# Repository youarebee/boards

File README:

Terminal blocks taken from here:
http://www.kicadlib.org/Fichiers/Ludek_libraries.html

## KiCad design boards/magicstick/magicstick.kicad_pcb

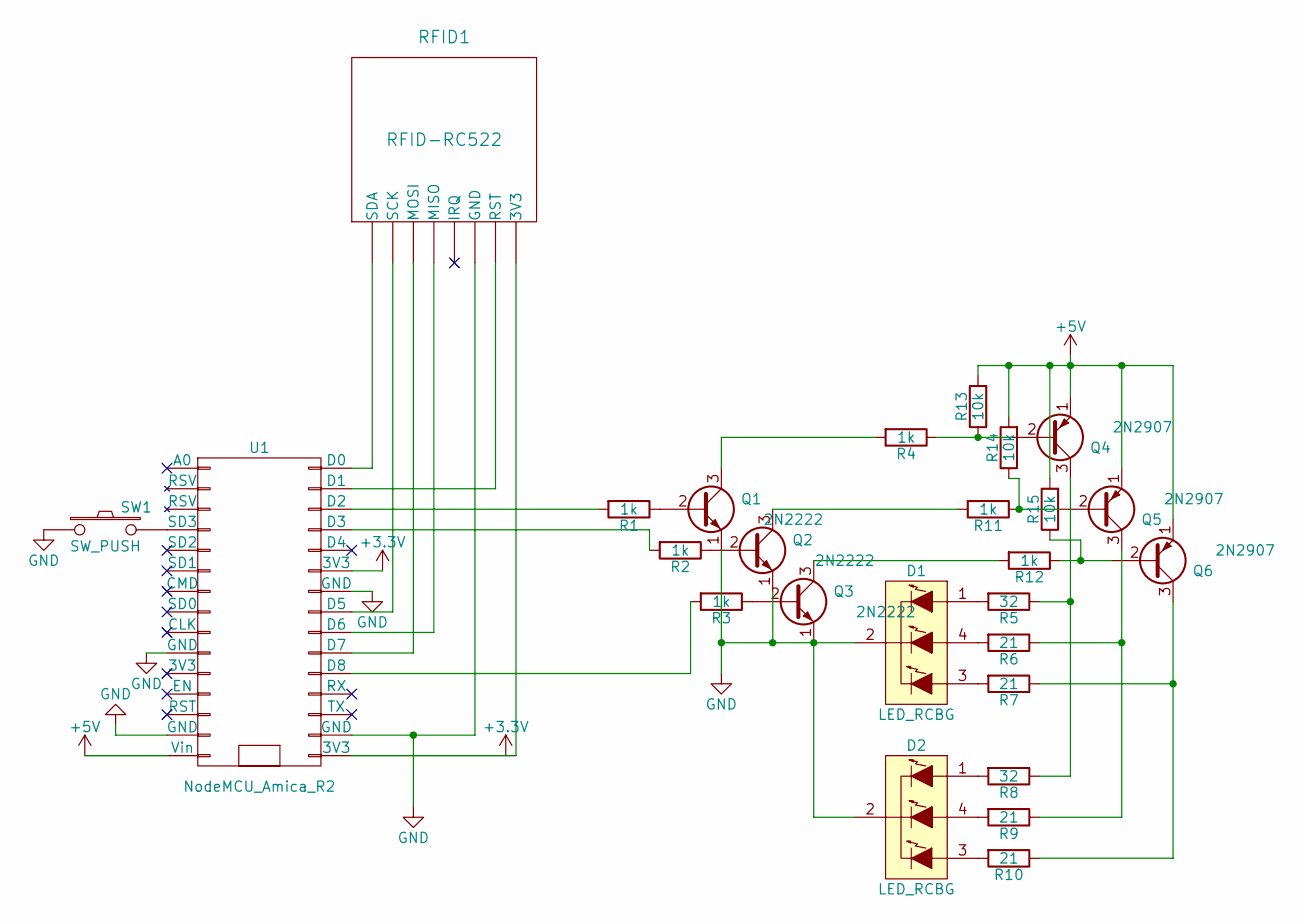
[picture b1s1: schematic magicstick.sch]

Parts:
D1, D2: LED_RCBG; LED-RGB-5MM_Common_Cathode
Q1, Q2, Q3: 2N2222; TO-92_Inline_Narrow_Oval
Q4, Q5, Q6: 2N2907; TO-92_Inline_Narrow_Oval
R1, R2, R3, R4, R11, R12: 1k; Resistor_Horizontal_RM10mm
R5, R8: 32; Resistor_Horizontal_RM10mm
R6, R7, R9, R10: 21; Resistor_Horizontal_RM10mm
R13, R14, R15: 10k; Resistor_Horizontal_RM10mm
RFID1: RFID-RC522; Pin_Header_Straight_1x08
SW1: SW_PUSH; SW_PUSH_SMALL
U1: NodeMCU_Amica_R2

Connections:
+5V: Q4.1 (E), Q5.1 (E), Q6.1 (E), R13.2, R14.2, R15.2, U1.15 (Vin)
GND: D1.2 (COMMON_CATHODE), D2.2 (COMMON_CATHODE), Q1.1 (E), Q2.1 (E), Q3.1 (E), RFID1.6 (GND), SW1.1, U1.10 (GND), U1.14 (GND), U1.17 (GND), U1.24 (GND)
unnamed: D1.1 (RED_ANODE), R5.2
unnamed: D1.3 (BLUE_ANODE), R7.2
unnamed: D1.4 (GREEN_ANODE), R6.2
unnamed: D2.1 (RED_ANODE), R8.2
unnamed: D2.3 (BLUE_ANODE), R10.2
unnamed: D2.4 (GREEN_ANODE), R9.2
unnamed: Q1.2 (B), R1.1
unnamed: Q1.3 (C), R4.2
unnamed: Q2.2 (B), R2.1
unnamed: Q2.3 (C), R11.2
unnamed: Q3.2 (B), R3.1
unnamed: Q3.3 (C), R12.2
unnamed: Q4.2 (B), R4.1, R13.1
unnamed: Q4.3 (C), R5.1, R8.1
unnamed: Q5.2 (B), R11.1, R14.1
unnamed: Q5.3 (C), R6.1, R9.1
unnamed: Q6.2 (B), R12.1, R15.1
unnamed: Q6.3 (C), R7.1, R10.1
unnamed: R1.2, U1.28 (D2)
unnamed: R2.2, U1.27 (D3)
unnamed: R3.2, U1.20 (D8)
unnamed: RFID1.1 (SDA), U1.30 (D0)
unnamed: RFID1.2 (SCK), U1.23 (D5)
unnamed: RFID1.3 (MOSI), U1.21 (D7)
unnamed: RFID1.4 (MISO), U1.22 (D6)
unnamed: RFID1.7 (RST), U1.29 (D1)
unnamed: SW1.2, U1.4 (SD3)

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
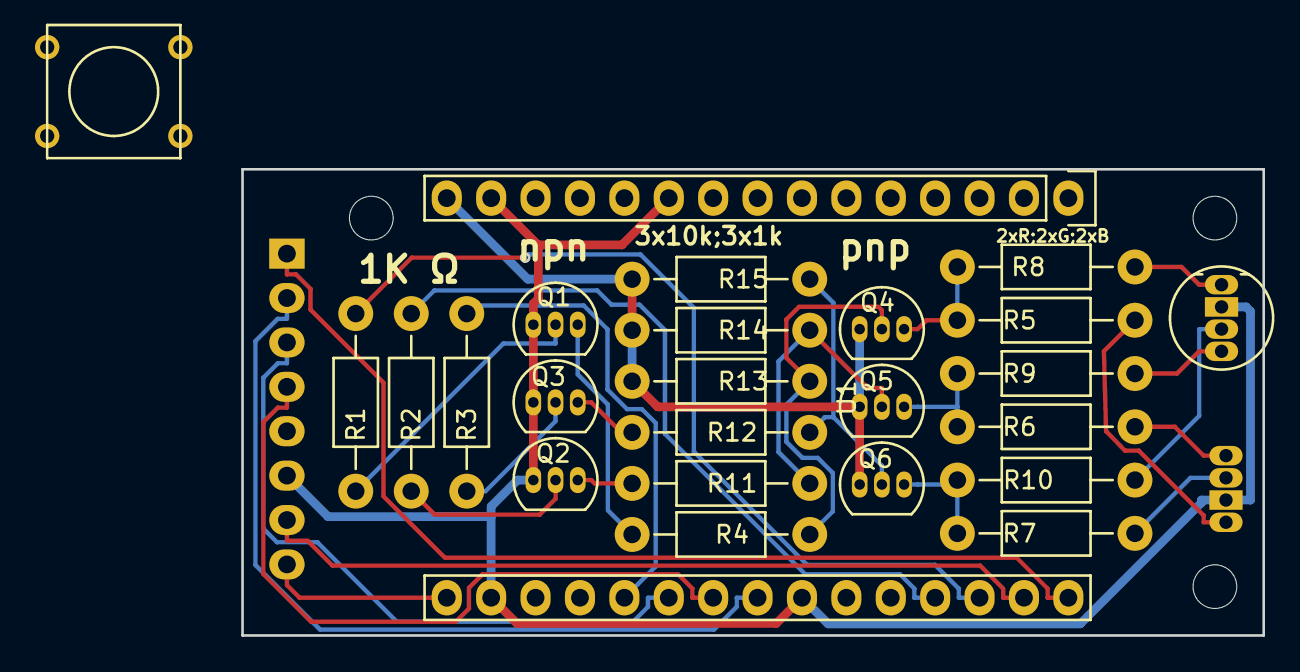
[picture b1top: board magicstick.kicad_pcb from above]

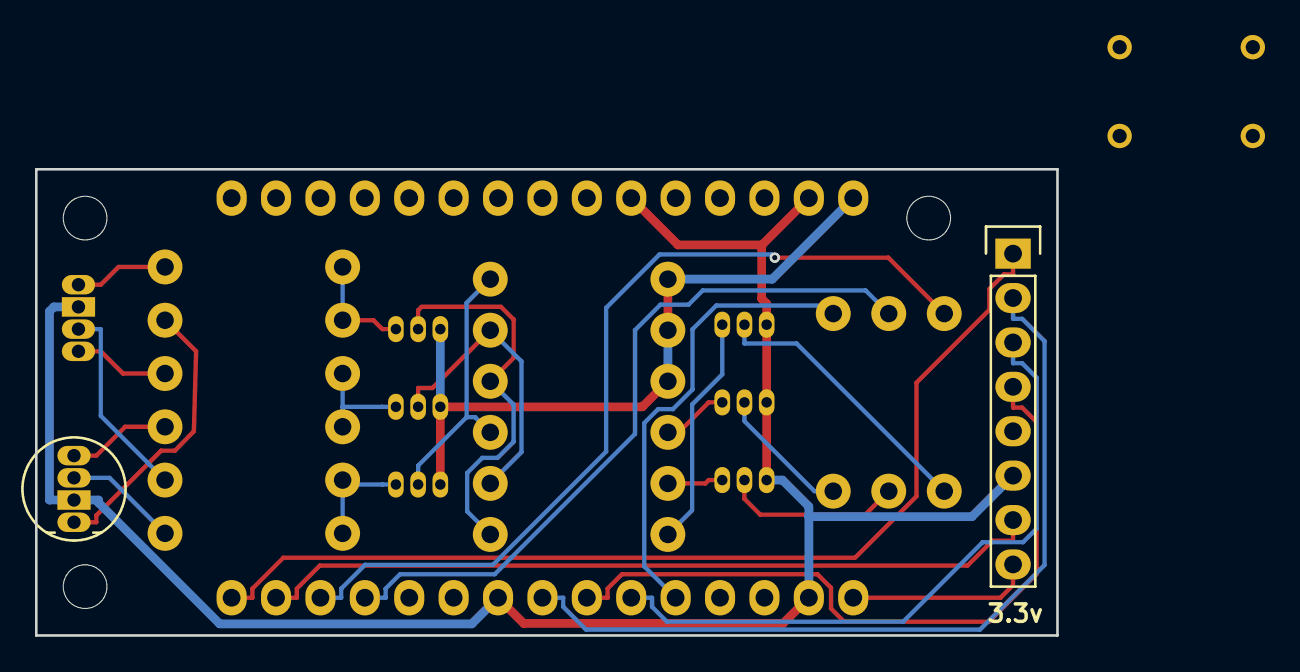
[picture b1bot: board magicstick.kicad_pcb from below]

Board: 2 copper layers, 58.4 x 26.7 mm, 29 parts (2 on the bottom side), 30 nets.

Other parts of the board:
REF1, REF3, REF4: MountingHole_2-5mm

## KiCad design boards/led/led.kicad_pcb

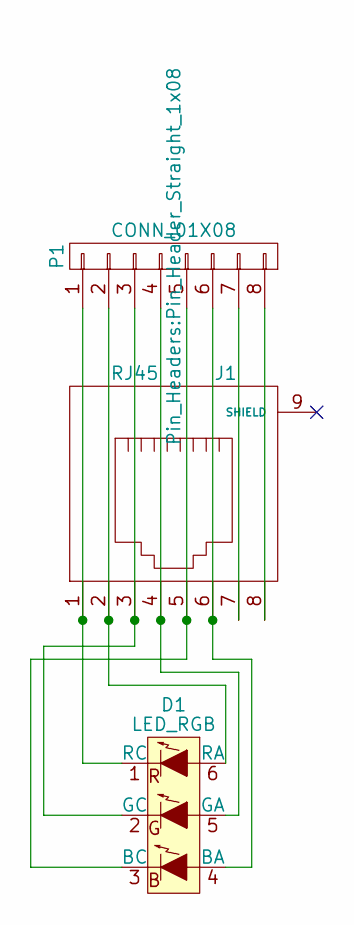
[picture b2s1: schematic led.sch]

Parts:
D1: LED_RGB; 10wled
J1: RJ45; RJ45_8
P1: CONN_01X08; Pin_Header_Straight_1x08

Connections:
unnamed: D1.1 (RC), J1.1, P1.1
unnamed: D1.2 (GC), J1.3, P1.3
unnamed: D1.3 (BC), J1.5, P1.5
unnamed: D1.4 (BA), J1.6, P1.6
unnamed: D1.5 (GA), J1.4, P1.4
unnamed: D1.6 (RA), J1.2, P1.2
unnamed: J1.7, P1.7
unnamed: J1.8, P1.8

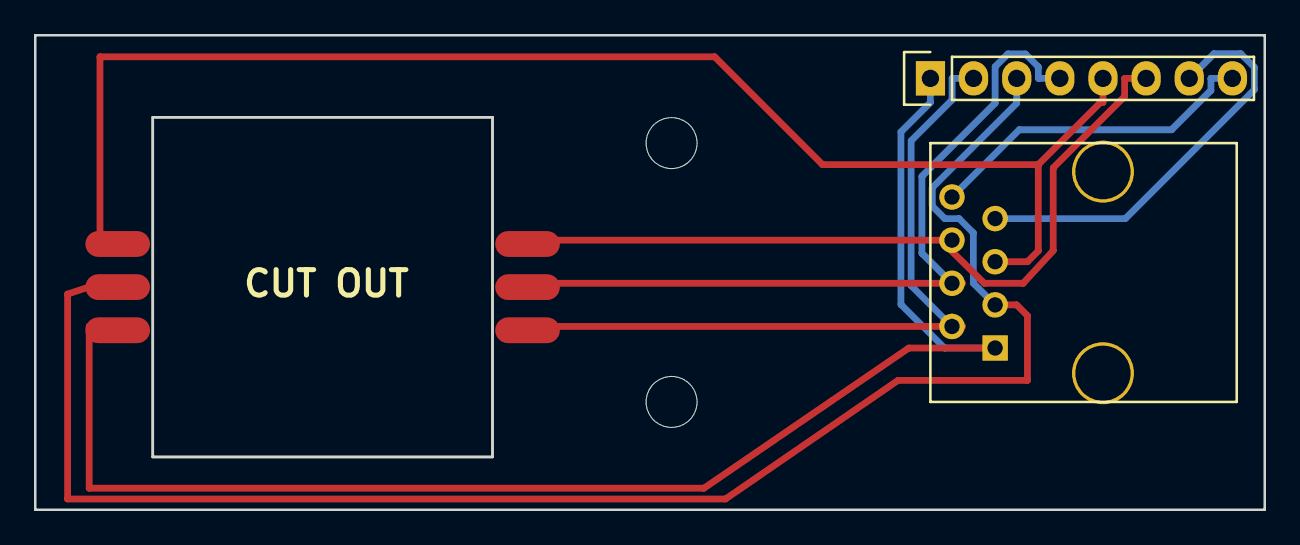
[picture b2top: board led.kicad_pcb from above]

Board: 2 copper layers, 72.4 x 27.9 mm, 5 parts (0 on the bottom side), 8 nets.

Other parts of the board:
REF1, REF2: MountingHole_2-5mm; MountingHole_3mm

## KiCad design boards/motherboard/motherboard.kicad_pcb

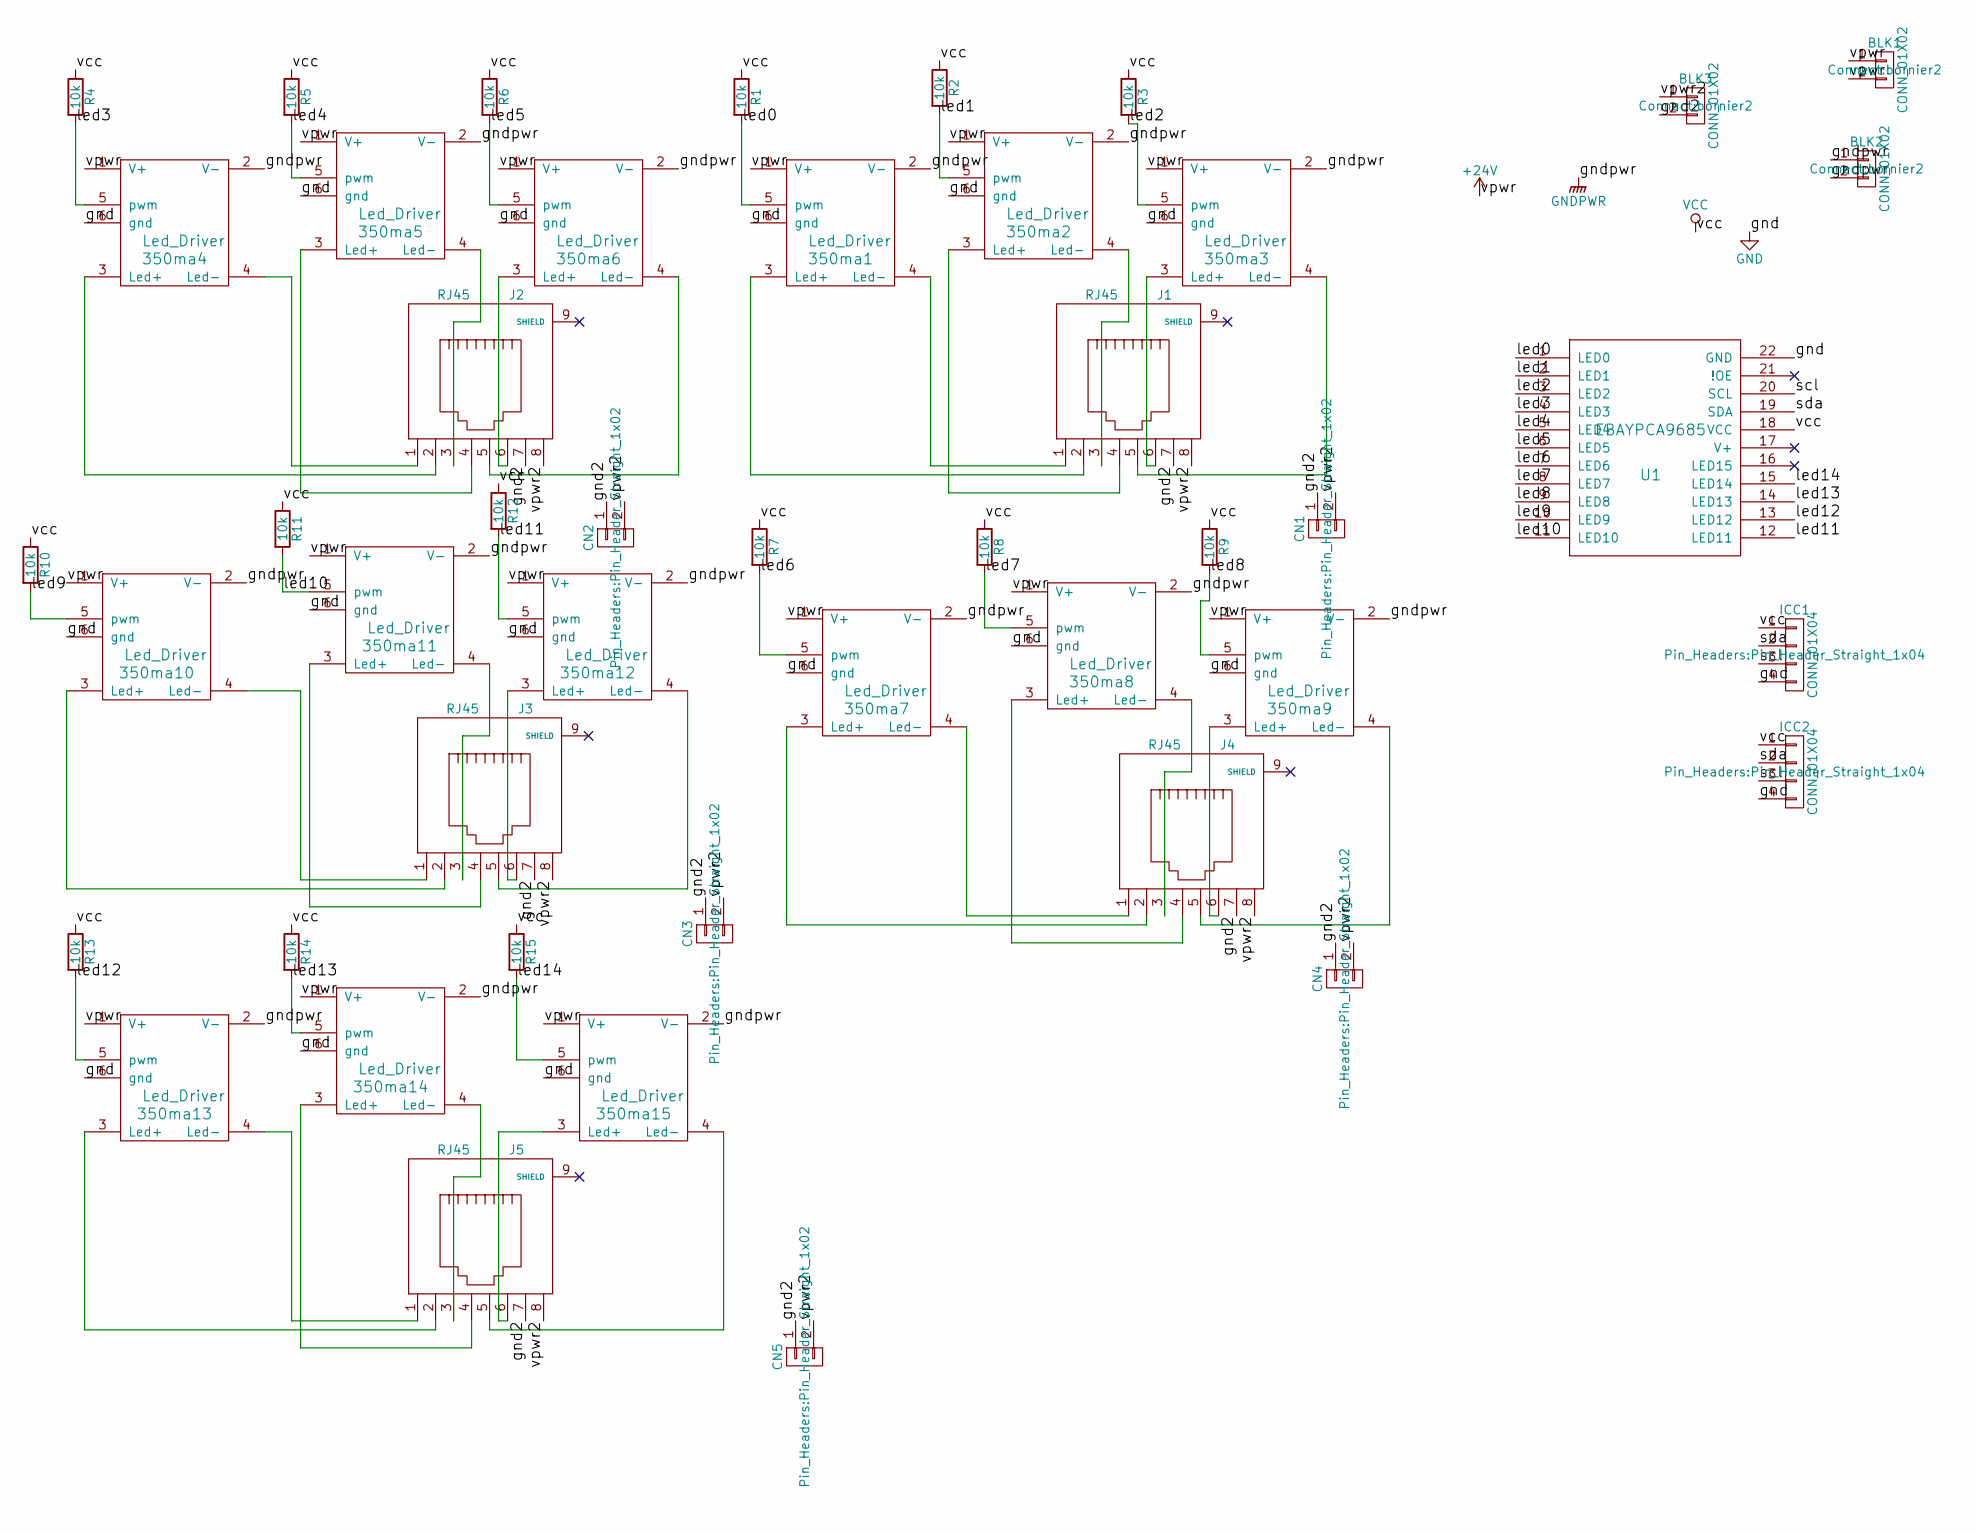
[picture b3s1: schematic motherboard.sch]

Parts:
350ma1, 350ma2, 350ma3, 350ma4, 350ma5, 350ma6, 350ma7, 350ma8, 350ma9, 350ma10, 350ma11, 350ma12, 350ma13, 350ma14, 350ma15: Led_Driver; 350ma_constant_current_xl4001
BLK1, BLK2, BLK3: CONN_01X02; bornier2
CN1, CN2, CN3, CN4, CN5: CONN_01X02; Pin_Header_Straight_1x02
ICC1, ICC2: CONN_01X04; Pin_Header_Straight_1x04
J1, J2, J3, J4, J5: RJ45; RJ45_8
R1, R2, R3, R4, R5, R6, R7, R8, R9, R10, R11, R12, R13, R14, R15: 10k; Resistor_Horizontal_RM10mm
U1: EBAYPCA9685

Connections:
+24V: 350ma1.1 (V+), 350ma2.1 (V+), 350ma3.1 (V+), 350ma4.1 (V+), 350ma5.1 (V+), 350ma6.1 (V+), 350ma7.1 (V+), 350ma8.1 (V+), 350ma9.1 (V+), 350ma10.1 (V+), 350ma11.1 (V+), 350ma12.1 (V+), 350ma13.1 (V+), 350ma14.1 (V+), 350ma15.1 (V+), BLK1.1, BLK1.2
/gnd2: BLK3.2, CN1.1, CN2.1, CN3.1, CN4.1, CN5.1, J1.7, J2.7, J3.7, J4.7, J5.7
/led0: 350ma1.5 (pwm), R1.2, U1.1 (LED0)
/led1: 350ma2.5 (pwm), R2.2, U1.2 (LED1)
/led2: 350ma3.5 (pwm), R3.2, U1.3 (LED2)
/led3: 350ma4.5 (pwm), R4.2, U1.4 (LED3)
/led4: 350ma5.5 (pwm), R5.2, U1.5 (LED4)
/led5: 350ma6.5 (pwm), R6.2, U1.6 (LED5)
/led6: 350ma7.5 (pwm), R7.2, U1.7 (LED6)
/led7: 350ma8.5 (pwm), R8.2, U1.8 (LED7)
/led8: 350ma9.5 (pwm), R9.2, U1.9 (LED8)
/led9: 350ma10.5 (pwm), R10.2, U1.10 (LED9)
/led10: 350ma11.5 (pwm), R11.2, U1.11 (LED10)
/led11: 350ma12.5 (pwm), R12.2, U1.12 (LED11)
/led12: 350ma13.5 (pwm), R13.2, U1.13 (LED12)
/led13: 350ma14.5 (pwm), R14.2, U1.14 (LED13)
/led14: 350ma15.5 (pwm), R15.2, U1.15 (LED14)
/scl: ICC1.3, ICC2.3, U1.20 (SCL), U1.26 (SCL)
/sda: ICC1.2, ICC2.2, U1.19 (SDA), U1.25 (SDA)
/vpwr2: BLK3.1, CN1.2, CN2.2, CN3.2, CN4.2, CN5.2, J1.8, J2.8, J3.8, J4.8, J5.8
GND: 350ma1.6 (gnd), 350ma2.6 (gnd), 350ma3.6 (gnd), 350ma4.6 (gnd), 350ma5.6 (gnd), 350ma6.6 (gnd), 350ma7.6 (gnd), 350ma8.6 (gnd), 350ma9.6 (gnd), 350ma10.6 (gnd), 350ma11.6 (gnd), 350ma12.6 (gnd), 350ma13.6 (gnd), 350ma14.6 (gnd), 350ma15.6 (gnd), ICC1.4, ICC2.4, U1.22 (GND), U1.28 (GND)
GNDPWR: 350ma1.2 (V-), 350ma2.2 (V-), 350ma3.2 (V-), 350ma4.2 (V-), 350ma5.2 (V-), 350ma6.2 (V-), 350ma7.2 (V-), 350ma8.2 (V-), 350ma9.2 (V-), 350ma10.2 (V-), 350ma11.2 (V-), 350ma12.2 (V-), 350ma13.2 (V-), 350ma14.2 (V-), 350ma15.2 (V-), BLK2.1, BLK2.2
unnamed: 350ma1.3 (Led+), J1.2
unnamed: 350ma1.4 (Led-), J1.1
unnamed: 350ma2.3 (Led+), J1.4
unnamed: 350ma2.4 (Led-), J1.3
unnamed: 350ma3.3 (Led+), J1.6
unnamed: 350ma3.4 (Led-), J1.5
unnamed: 350ma4.3 (Led+), J2.2
unnamed: 350ma4.4 (Led-), J2.1
unnamed: 350ma5.3 (Led+), J2.4
unnamed: 350ma5.4 (Led-), J2.3
unnamed: 350ma6.3 (Led+), J2.6
unnamed: 350ma6.4 (Led-), J2.5
unnamed: 350ma7.3 (Led+), J4.2
unnamed: 350ma7.4 (Led-), J4.1
unnamed: 350ma8.3 (Led+), J4.4
unnamed: 350ma8.4 (Led-), J4.3
unnamed: 350ma9.3 (Led+), J4.6
unnamed: 350ma9.4 (Led-), J4.5
unnamed: 350ma10.3 (Led+), J3.2
unnamed: 350ma10.4 (Led-), J3.1
unnamed: 350ma11.3 (Led+), J3.4
unnamed: 350ma11.4 (Led-), J3.3
unnamed: 350ma12.3 (Led+), J3.6
unnamed: 350ma12.4 (Led-), J3.5
unnamed: 350ma13.3 (Led+), J5.2
unnamed: 350ma13.4 (Led-), J5.1
unnamed: 350ma14.3 (Led+), J5.4
unnamed: 350ma14.4 (Led-), J5.3
unnamed: 350ma15.3 (Led+), J5.6
unnamed: 350ma15.4 (Led-), J5.5
unnamed: U1.21 (!OE), U1.27 (!OE)
V+: U1.17 (V+), U1.23 (V+)
VCC: ICC1.1, ICC2.1, R1.1, R2.1, R3.1, R4.1, R5.1, R6.1, R7.1, R8.1, R9.1, R10.1, R11.1, R12.1, R13.1, R14.1, R15.1, U1.18 (VCC), U1.24 (VCC)

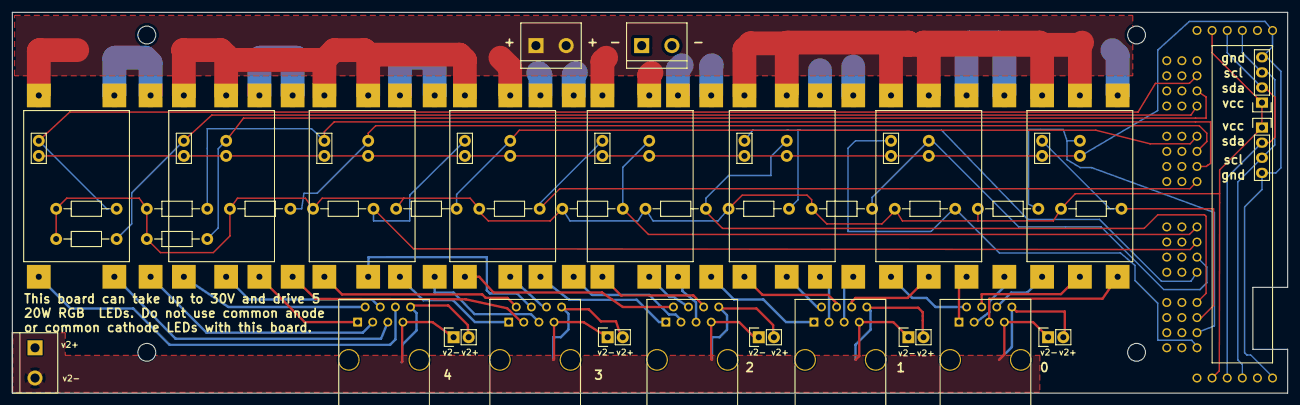
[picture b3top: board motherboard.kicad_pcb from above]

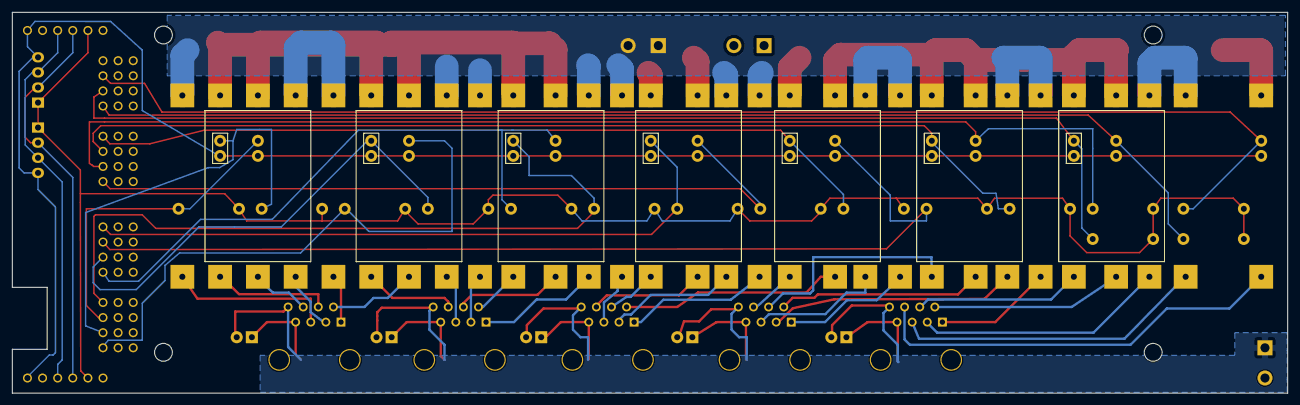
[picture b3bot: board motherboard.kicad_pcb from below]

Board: 2 copper layers, 214.4 x 64.0 mm, 50 parts (7 on the bottom side), 55 nets.

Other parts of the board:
REF2, REF3, REF10, REF11: MountingHole; MountingHole_3mm

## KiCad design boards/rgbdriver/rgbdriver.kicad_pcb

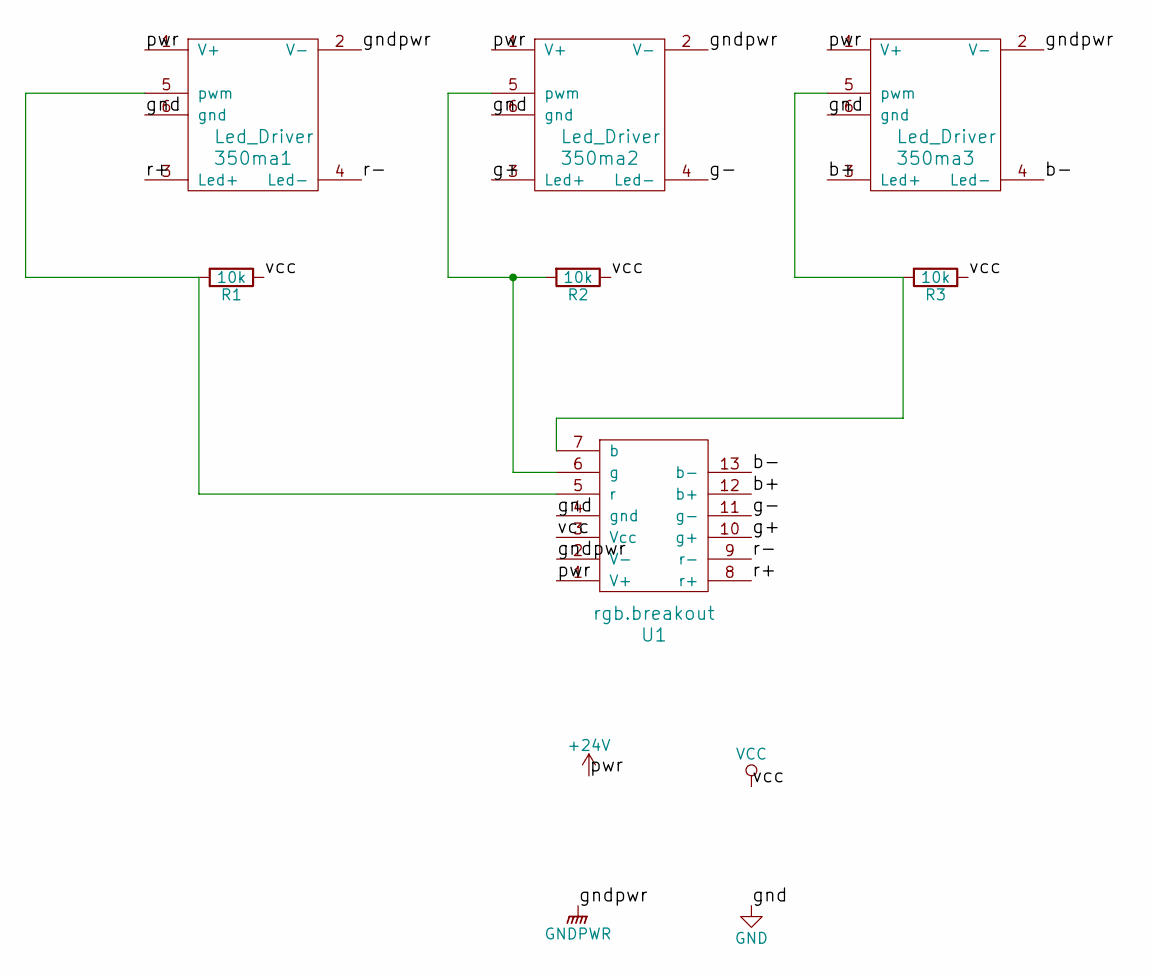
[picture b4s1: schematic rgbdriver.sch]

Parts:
350ma1, 350ma2, 350ma3: Led_Driver; 350ma constant current xl4001
R1, R2, R3: 10k; Resistor_Horizontal_RM10mm
U1: rgb.breakout

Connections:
+24V: 350ma1.1 (V+), 350ma2.1 (V+), 350ma3.1 (V+), U1.1 (V+)
/b+: 350ma3.3 (Led+), U1.12 (b+)
/b-: 350ma3.4 (Led-), U1.13 (b-)
/g+: 350ma2.3 (Led+), U1.10 (g+)
/g-: 350ma2.4 (Led-), U1.11 (g-)
/r+: 350ma1.3 (Led+), U1.8 (r+)
/r-: 350ma1.4 (Led-), U1.9 (r-)
GND: 350ma1.6 (gnd), 350ma2.6 (gnd), 350ma3.6 (gnd), U1.4 (gnd)
GNDPWR: 350ma1.2 (V-), 350ma2.2 (V-), 350ma3.2 (V-), U1.2 (V-)
unnamed: 350ma1.5 (pwm), R1.2, U1.5 (r)
unnamed: 350ma2.5 (pwm), R2.2, U1.6 (g)
unnamed: 350ma3.5 (pwm), R3.2, U1.7 (b)
VCC: R1.1, R2.1, R3.1, U1.3 (Vcc)

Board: 2 copper layers, 7 parts (1 on the bottom side), 13 nets, no tracks yet.

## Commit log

2016-07-01 scematic for driver pcb
2016-07-01 updated pcb
2016-07-01 first attempt at copper fill
2016-07-02 intigial magicstick design
2016-07-02 magic stick circuit
2016-07-02 minor changes
2016-07-02 starting board design for magic stick
2016-07-02 pcb for magic stick
2016-07-02 added filled zone
2016-07-02 minor rgb driver change
2016-07-03 autorouter + rj45
2016-07-03 magic stick updates
2016-07-14 initial mother board
2016-07-14 updates to mother board
2016-07-15 mother board pcb
2016-07-15 sort of ok
2016-07-15 before autoroute
2016-07-15 after route
2016-07-16 moved parts around and swapped pca footprint
2016-07-16 before auto route
2016-07-16 after auto route
2016-07-16 led pcb
2016-07-18 added zones
2016-07-18 another revision
2016-07-19 minor fix
2016-07-19 final changes
2016-07-22 added breakout for ethernet
2016-07-23 made a hole for capacitor
2016-07-25 sink
2016-07-27 no vias
2016-07-27 minor tweaks
2016-07-28 minor track changes
2016-08-06 pcb v1
2016-08-09 fixed cc foot print; now need to redo motherboard :(
